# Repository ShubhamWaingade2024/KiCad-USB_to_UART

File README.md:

#KiCad Project
*a nice little PCB*

This is my PCB, there are many little it but this one is mine.

##Schematic

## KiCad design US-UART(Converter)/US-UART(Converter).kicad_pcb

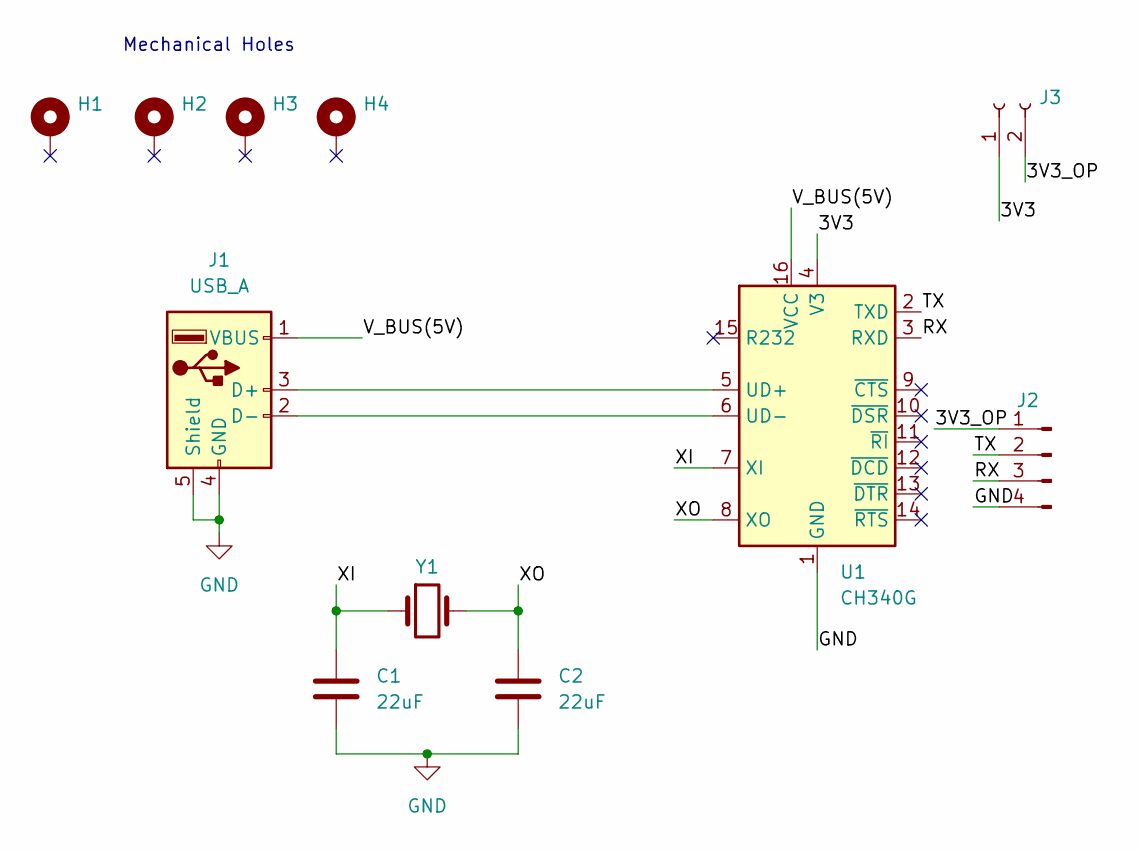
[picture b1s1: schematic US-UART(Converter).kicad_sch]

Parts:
C1, C2: 22uF; C_0201_0603Metric_Pad0.64x0.40mm_HandSolder
H1, H2, H3, H4: MountingHole_Pad; MountingHole_2.2mm_M2_DIN965_Pad
J1: USB_A; USB_A_Molex_48037-2200_Horizontal
J2: Conn_01x04_Pin; FanPinHeader_1x04_P2.54mm_Vertical
J3: Conn_01x02_Socket; PinHeader_1x02_P2.54mm_Horizontal
U1: CH340G; SOIC-16_3.9x9.9mm_P1.27mm
Y1: Crystal; Crystal_HC49-U_Horizontal

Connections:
/3V3: J3.1, U1.4 (V3)
/3V3_OP: J2.1, J3.2
/RX: J2.3, U1.3 (RXD)
/TX: J2.2, U1.2 (TXD)
/V_BUS(5V): J1.1 (VBUS), U1.16 (VCC)
/XI: C1.1, U1.7 (XI), Y1.1
/XO: C2.1, U1.8 (XO), Y1.2
GND: C1.2, C2.2, J1.4 (GND), J1.5 (Shield), J2.4, U1.1 (GND)
unnamed: J1.3 (D+), U1.5 (UD+)
unnamed: J1.2 (D-), U1.6 (UD-)

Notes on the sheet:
Mechanical Holes

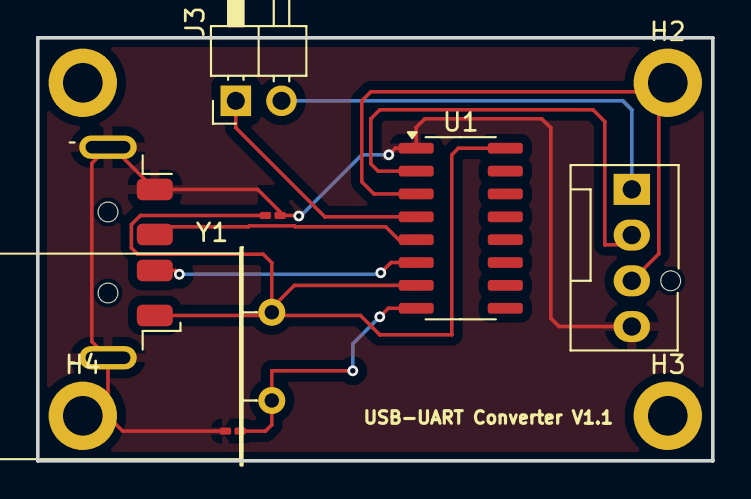
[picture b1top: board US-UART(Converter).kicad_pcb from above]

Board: 2 copper layers, 37.5 x 23.5 mm, 11 parts (0 on the bottom side), 10 nets.
